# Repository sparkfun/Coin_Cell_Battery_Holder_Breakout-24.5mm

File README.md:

**NOTE:** *This product has been retired from our catalog. If you are looking for more up-to-date info, please check out some of these resources to see how other users are still hacking and improving on this product.*
* *[SparkFun Forum](https://forum.sparkfun.com/)*
* *[IRC Channel](https://www.sparkfun.com/news/263)*

SparkFun Coin Cell Battery Holder Breakout - 24.5mm (PTH)
===========================================================

[*SparkFun Coin Cell Battery Holder Breakout - 24.5mm (PTH) (BOB-10495)*](https://www.sparkfun.com/products/10495)

This is a simple breakout board for our through-hole 24.5 mm coin cell holder.

Repository Contents
-------------------

* **/Hardware** - Eagle design files (.brd, .sch)

Documentation
--------------
* **[SparkFun Fritzing repo](https://github.com/sparkfun/Fritzing_Parts)** - Fritzing diagrams for SparkFun products.
* **[SparkFun 3D Model repo](https://github.com/sparkfun/3D_Models)** - 3D models of SparkFun products. 

License Information
-------------------
This product is _**open source**_! 

The **hardware** is released under [Creative Commons ShareAlike 4.0 International](https://creativecommons.org/licenses/by-sa/4.0/).

Please use, reuse, and modify these files as you see fit. Please maintain attribution to SparkFun Electronics and release anything derivative under the same license.

Distributed as-is; no warranty is given.

- Your friends at SparkFun.

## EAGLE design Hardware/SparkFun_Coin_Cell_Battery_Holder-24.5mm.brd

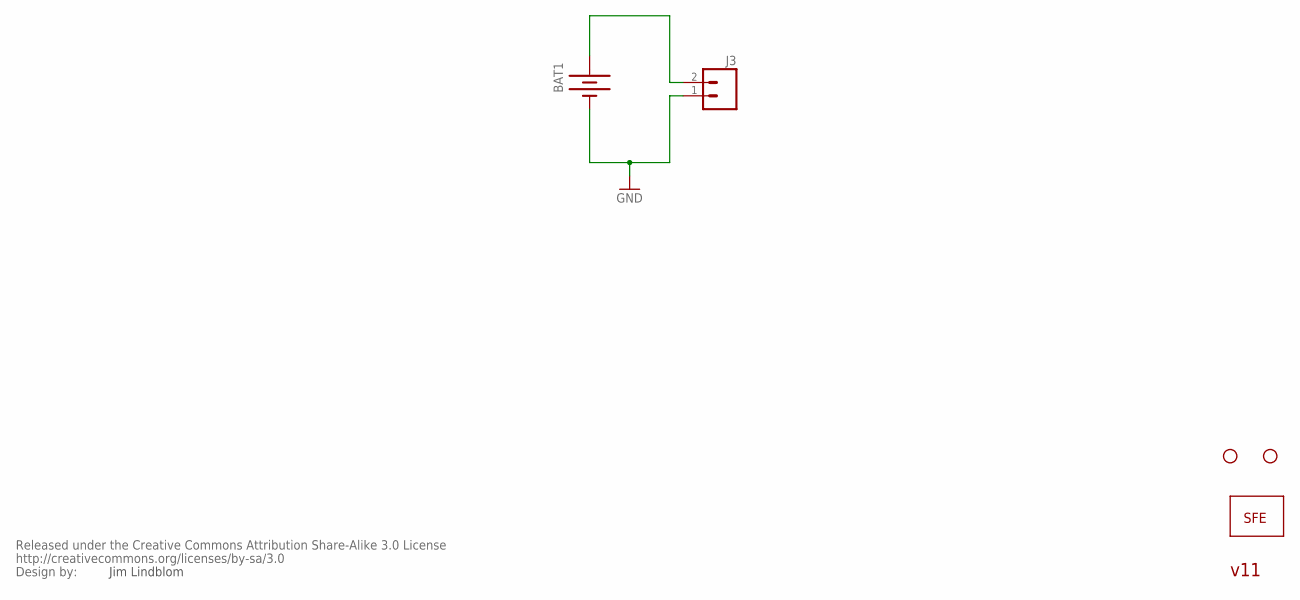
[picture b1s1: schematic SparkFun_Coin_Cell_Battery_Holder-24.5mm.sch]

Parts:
BAT1: BATTERY245PTH; BATTCON_245MM_PTH
J3: M02PTH; 1X02
JP2: LOGO-SFENEW; SFE-NEW-WEBLOGO
JP4, JP5: STAND-OFF
U$1: CREATIVE_COMMONS

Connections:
GND: BAT1.2 (-), J3.1
J2: BAT1.3 (+), J3.2

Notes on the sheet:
Jim Lindblom
v11

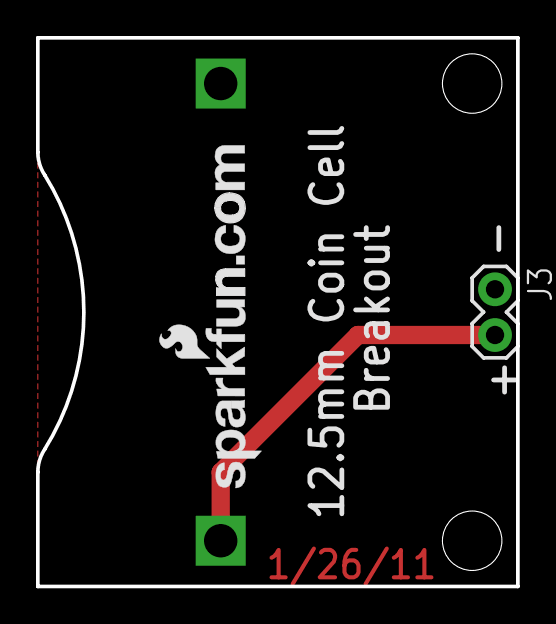
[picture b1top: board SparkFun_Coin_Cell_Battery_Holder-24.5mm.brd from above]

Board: 2 copper layers, 26.7 x 30.5 mm, 6 parts (1 on the bottom side), 2 nets.

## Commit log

2015-05-06 Adding hardware files

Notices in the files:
parts and their libraries:
SparkFun: Released under the Creative Commons Attribution Share-Alike 3.0 License
SparkFun: http://creativecommons.org/licenses/by-sa/3.0
